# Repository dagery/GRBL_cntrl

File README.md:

# Univerasal board for arduino nano with GRBL
------

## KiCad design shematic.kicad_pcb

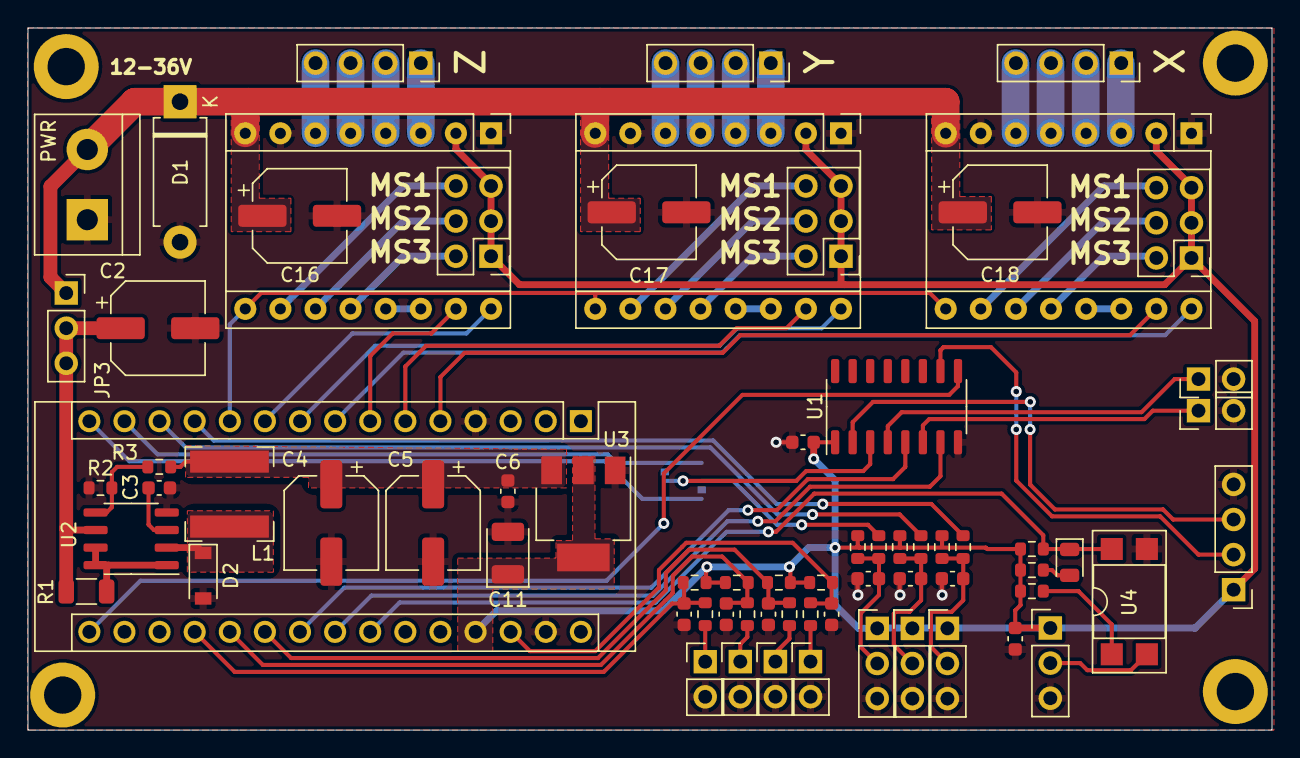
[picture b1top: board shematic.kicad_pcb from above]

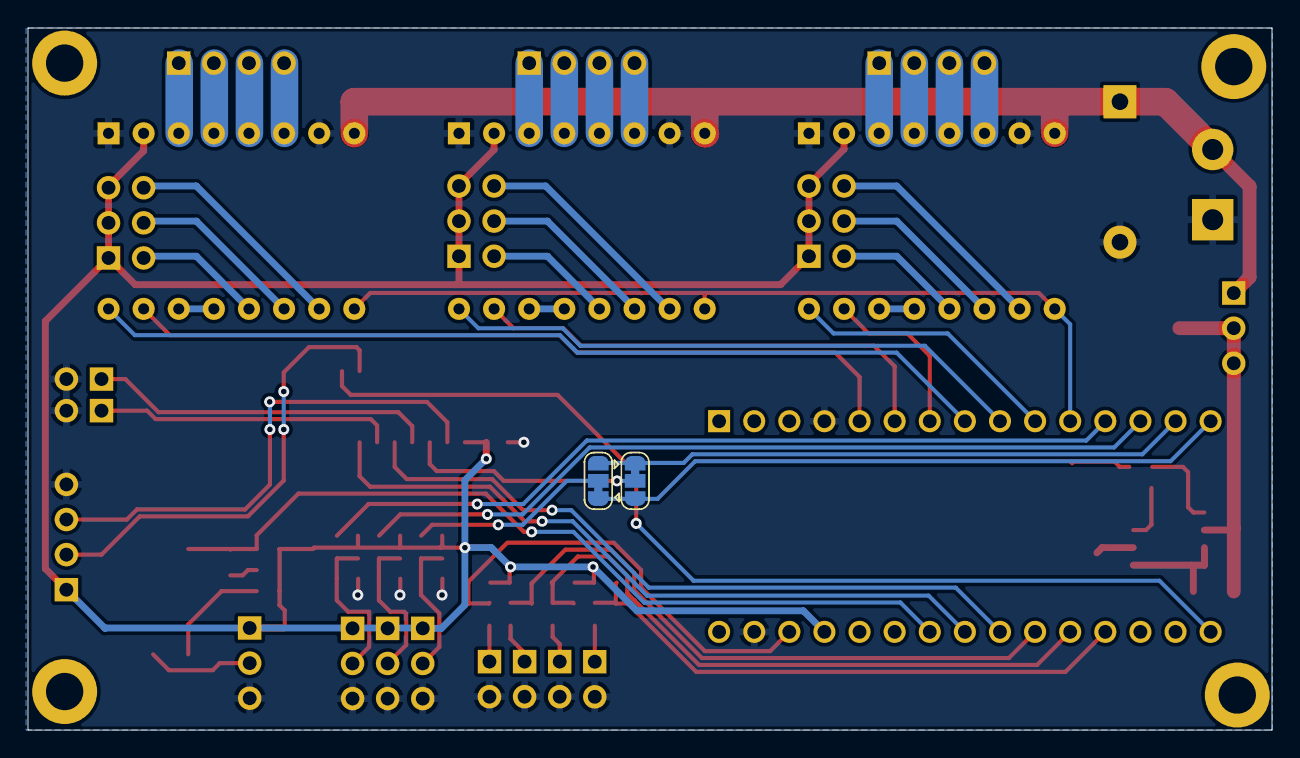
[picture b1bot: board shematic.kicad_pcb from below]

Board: 2 copper layers, 90.0 x 50.8 mm, 71 parts (2 on the bottom side), 68 nets.

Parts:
A1: Arduino_Nano_v3.x; Arduino_Nano
A2, A3, A4: Pololu_Breakout_A4988; Pololu_Breakout-16_15.2x20.3mm
C1, C6, C8, C9, C10, C12, C13, C14, C15: 100n; C_0603_1608Metric
C2, C18: 47u; CP_Elec_6.3x7.7
C3: 470p; C_0603_1608Metric
C4, C5: 100u; CP_Elec_6.3x4.9
C7: 100; C_0603_1608Metric
C11: 10u; CP_EIA-3528-21_Kemet-B
C16, C17: 100u; CP_Elec_6.3x7.7
D1: 1.5KExxA; D_DO-15_P10.16mm_Horizontal
D2: 1N5819; D_SOD-123
D3: LED; LED_0805_2012Metric
J2: MIST_ENB; PinHeader_1x02_P2.54mm_Vertical
J3: COOL_ENB; PinHeader_1x02_P2.54mm_Vertical
J4: SP/LAS; PinHeader_1x04_P2.54mm_Vertical
J5: PROBE; PinHeader_1x03_P2.54mm_Vertical
J6: LIM_X; PinHeader_1x03_P2.54mm_Vertical
J7: LIM_Y; PinHeader_1x03_P2.54mm_Vertical
J8: LIM_Z; PinHeader_1x03_P2.54mm_Vertical
J9: ESTOP; PinHeader_1x02_P2.54mm_Vertical
J10: FHOLD; PinHeader_1x02_P2.54mm_Vertical
J11: SRESU; PinHeader_1x02_P2.54mm_Vertical
J12: RESET; PinHeader_1x02_P2.54mm_Vertical
J13, J14, J15: Conn_02x03_Odd_Even; PinHeader_2x03_P2.54mm_Vertical
JP1: VAR_SP; SolderJumper-3_P1.3mm_Bridged12_RoundedPad1.0x1.5mm
JP2: LIM_Z; SolderJumper-3_P1.3mm_Bridged12_RoundedPad1.0x1.5mm
JP3: EXT_PWR; PinSocket_1x03_P2.54mm_Vertical
L1: 220uH; L_Bourns-SRN6028
PWR: VIN; TerminalBlock_bornier-2_P5.08mm
R1: 0.33; R_1206_3216Metric
R2: 1.2K; R_0603_1608Metric
R3: 3.6K; R_0603_1608Metric
R4, R8, R9, R10, R12, R13, R14, R15, R16: 1k; R_0603_1608Metric
R5, R6, R7, R11, R17, R18, R19, R20: 10k; R_0603_1608Metric
U1: 4050; SO-16_3.9x9.9mm_P1.27mm
U2: MC34063AD; SO-8_3.9x4.9mm_P1.27mm
U3: AZ1117-5.0; SOT-223-3_TabPin2
U4: PC817; DIP-4_W7.62mm_SMDSocket_SmallPads
X: X; PinSocket_1x04_P2.54mm_Vertical
Y: Y; PinSocket_1x04_P2.54mm_Vertical
Z: Z; PinSocket_1x04_P2.54mm_Vertical

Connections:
+5V: A1.27 (+5V), A2.2 (VDD), A3.2 (VDD), A4.2 (VDD), C1.2, C7.1, C11.1, J4.1, J5.1, J6.1, J7.1, J8.1, J13.1, J13.3, J13.5, J14.1, J14.3, J14.5, J15.1, J15.3, J15.5, R4.1, R5.1, R6.1, R7.1, R11.1, R12.1, R17.1, R18.1, R19.1, R20.1, U1.1 (VCC), U3.2 (VO)
+10V: C4.1, C5.1, C6.1, L1.2, R3.1, U3.3 (VI)
/COOL_EN: A1.22 (A3), U1.5
/DIR_X: A1.8 (D5), A2.16 (DIR)
/DIR_Y: A1.9 (D6), A3.16 (DIR)
/DIR_Z: A1.10 (D7), A4.16 (DIR)
/ESTOP: A1.28 (~RESET), C12.1, R13.1, R17.2
/FHOLD: A1.20 (A1), C13.1, R14.1, R18.2
/LIM_X: A1.12 (D9), R8.1
/LIM_Y: A1.13 (D10), R9.1
/LIM_Z: JP2.2 (C), R10.1
/MIST_EN: A1.23 (A4), U1.7
/PROBE: A1.24 (A5), D3.1 (K), R11.2, U4.4
/RESAB: A1.19 (A0), C15.1, R16.1, R20.2
/SP_DIR: A1.16 (D13), U1.9
/SP_PWM: JP1.2 (C), U1.3
/SRESU: A1.21 (A2), C14.1, R15.1, R19.2
/STEP_X: A1.5 (D2), A2.15 (STEP)
/STEP_Y: A1.6 (D3), A3.15 (STEP)
/STEP_Z: A1.7 (D4), A4.15 (STEP)
/~EN: A1.11 (D8), A2.9 (~ENABLE), A3.9 (~ENABLE), A4.9 (~ENABLE)
GND: A1.4 (GND), A1.29 (GND), A2.1 (GND), A2.7 (GND), A3.1 (GND), A3.7 (GND), A4.1 (GND), A4.7 (GND), C1.1, C2.2, C3.2, C4.2, C5.2, C6.2, C7.2, C8.2, C9.2, C10.2, C11.2, C12.2, C13.2, C14.2, C15.2, C16.2, C17.2, C18.2, D1.2 (A2), D2.2 (A), J2.2, J3.2, J4.4, J5.3, J6.3, J7.3, J8.3, J9.2, J10.2, J11.2, J12.2, PWR.1, R2.1, U1.8 (VSS), U2.4 (GND), U3.1 (GND), U4.3
unnamed: A1.14 (D11), JP1.1 (A), JP2.3 (B)
unnamed: A1.15 (D12), JP1.3 (B), JP2.1 (A)
unnamed: A2.3 (1B), X.1
unnamed: A2.4 (1A), X.2
unnamed: A2.5 (2A), X.3
unnamed: A2.6 (2B), X.4
unnamed: A2.10 (MS1), J13.6
unnamed: A2.11 (MS2), J13.4
unnamed: A2.12 (MS3), J13.2
unnamed: A2.13 (~RESET), A2.14 (~SLEEP)
unnamed: A3.3 (1B), Y.1
unnamed: A3.4 (1A), Y.2
unnamed: A3.5 (2A), Y.3
unnamed: A3.6 (2B), Y.4
unnamed: A3.10 (MS1), J14.6
unnamed: A3.11 (MS2), J14.4
unnamed: A3.12 (MS3), J14.2
unnamed: A3.13 (~RESET), A3.14 (~SLEEP)
unnamed: A4.3 (1B), Z.1
unnamed: A4.4 (1A), Z.2
unnamed: A4.5 (2A), Z.3
unnamed: A4.6 (2B), Z.4
unnamed: A4.10 (MS1), J15.6
unnamed: A4.11 (MS2), J15.4
unnamed: A4.12 (MS3), J15.2
unnamed: A4.13 (~RESET), A4.14 (~SLEEP)
unnamed: C2.1, JP3.2 (C), JP3.3 (B), R1.2, U2.6 (Vin)
unnamed: C3.1, U2.3 (TC)
unnamed: C8.1, J6.2, R5.2, R8.2
unnamed: C9.1, J7.2, R6.2, R9.2
unnamed: C10.1, J8.2, R7.2, R10.2
unnamed: D2.1 (K), L1.1, U2.2 (SwE)
unnamed: D3.2 (A), R12.2
unnamed: J2.1, U1.6
unnamed: J3.1, U1.4
unnamed: J4.3, U1.2
unnamed: J5.2, U4.2
unnamed: J9.1, R13.2
unnamed: J10.1, R14.2
unnamed: J11.1, R15.2
unnamed: J12.1, R16.2
unnamed: R1.1, U2.1 (SwC), U2.7 (Ipk), U2.8 (DC)
unnamed: R2.2, R3.2, U2.5 (Vfb)
unnamed: R4.2, U4.1
unnamed: J4.2, U1.10
VCC: A2.8 (VMOT), A3.8 (VMOT), A4.8 (VMOT), C16.1, C17.1, C18.1, D1.1 (A1), JP3.1 (A), PWR.2

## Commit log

2022-01-02 replaced footprints for passive component, edited silkscreens
